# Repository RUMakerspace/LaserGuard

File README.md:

# LaserGuard
Laser lockout system used by disabling USB traces via relay.

## LASERGUARD IS NOT A SAFETY MECHANISM AND SHOULD NOT BE USED AS SUCH.

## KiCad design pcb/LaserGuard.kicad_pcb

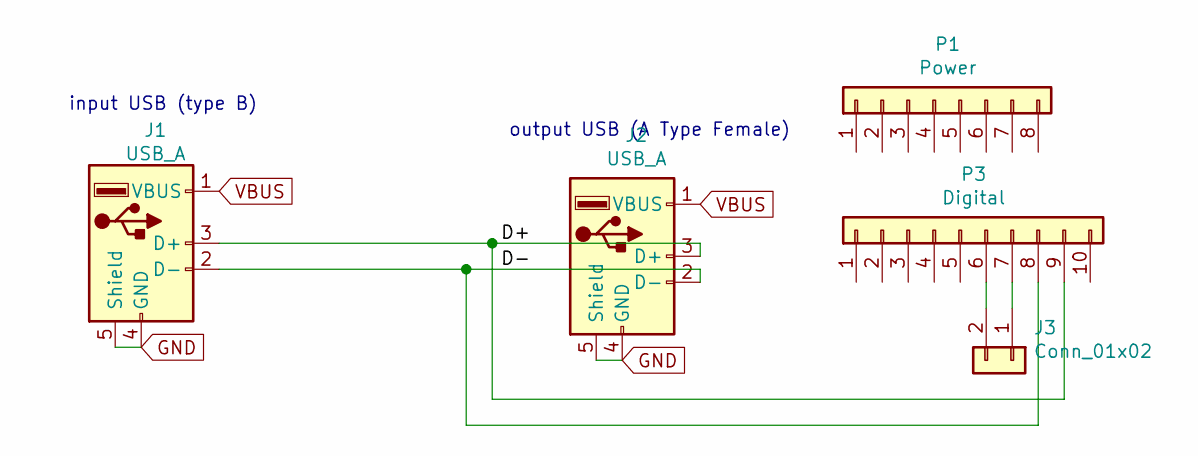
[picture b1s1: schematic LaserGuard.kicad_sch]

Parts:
J1: USB_A; USB_B_OST_USB-B1HSxx_Horizontal
J2: USB_A; USB_A_Molex_67643_Horizontal
J3: Conn_01x02; PinHeader_1x02_P2.54mm_Vertical
P1: Power; Socket_Strip_Arduino_1x08
P3: Digital; Socket_Strip_Arduino_1x10

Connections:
/D+: J1.3 (D+), J2.3 (D+), P3.9
/D-: J1.2 (D-), J2.2 (D-), P3.8
GND: J1.4 (GND), J1.5 (Shield), J2.4 (GND), J2.5 (Shield)
unnamed: J3.1, P3.7
unnamed: J3.2, P3.6
VBUS: J1.1 (VBUS), J2.1 (VBUS)

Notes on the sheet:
input USB (type B)
output USB (A Type Female)

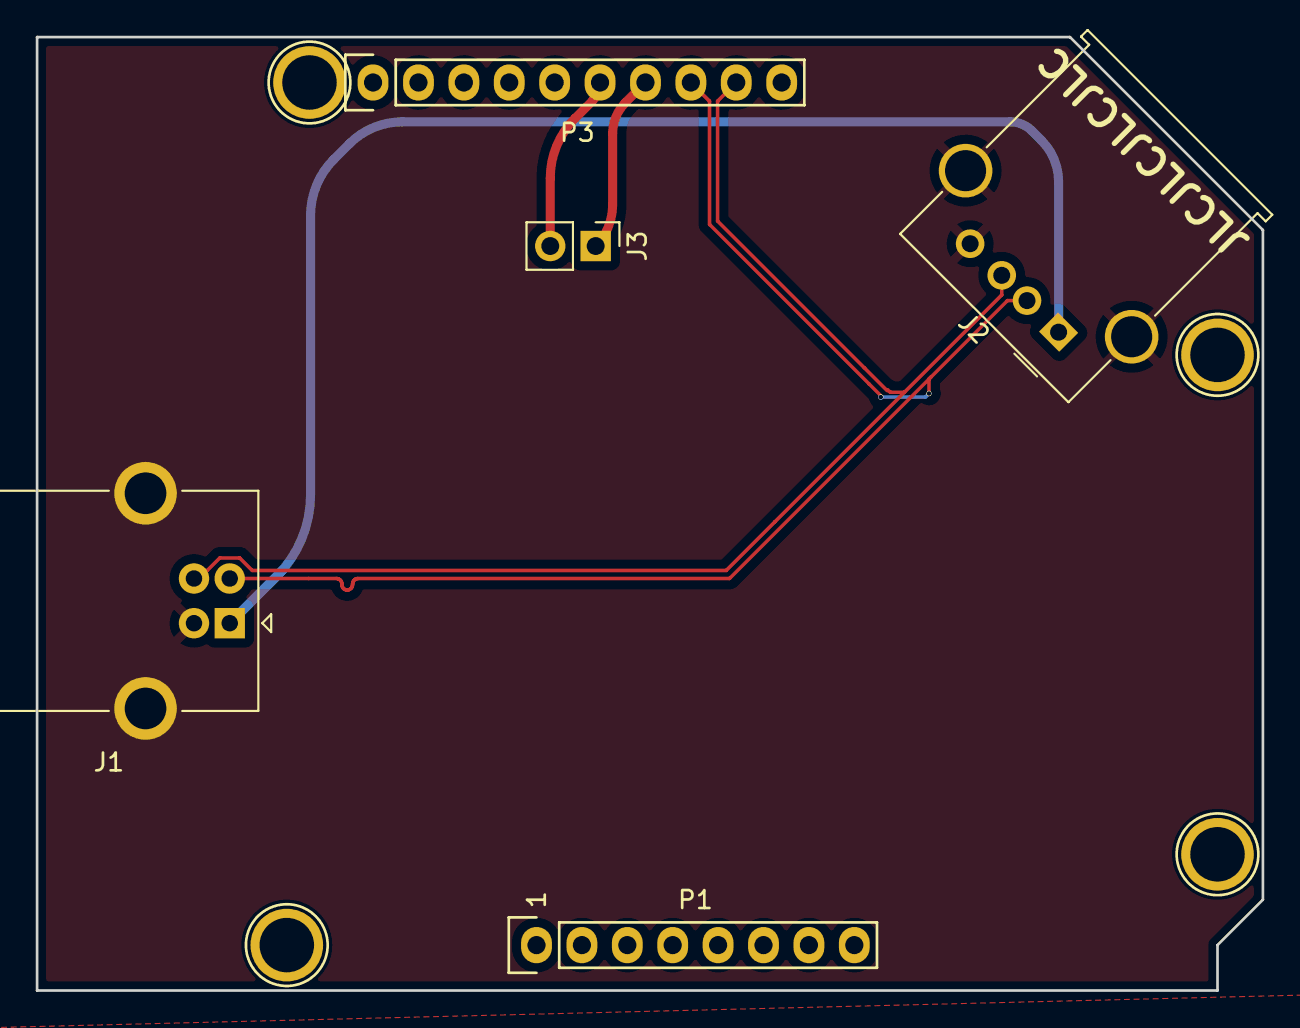
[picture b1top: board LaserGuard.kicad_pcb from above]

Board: 2 copper layers, 68.6 x 53.3 mm, 9 parts (0 on the bottom side), 6 nets.

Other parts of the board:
P5, P6, P7, P8: CONN_01X01; Arduino_1pin

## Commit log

2021-04-07 Initial import.
2021-04-07 modified: README.md
